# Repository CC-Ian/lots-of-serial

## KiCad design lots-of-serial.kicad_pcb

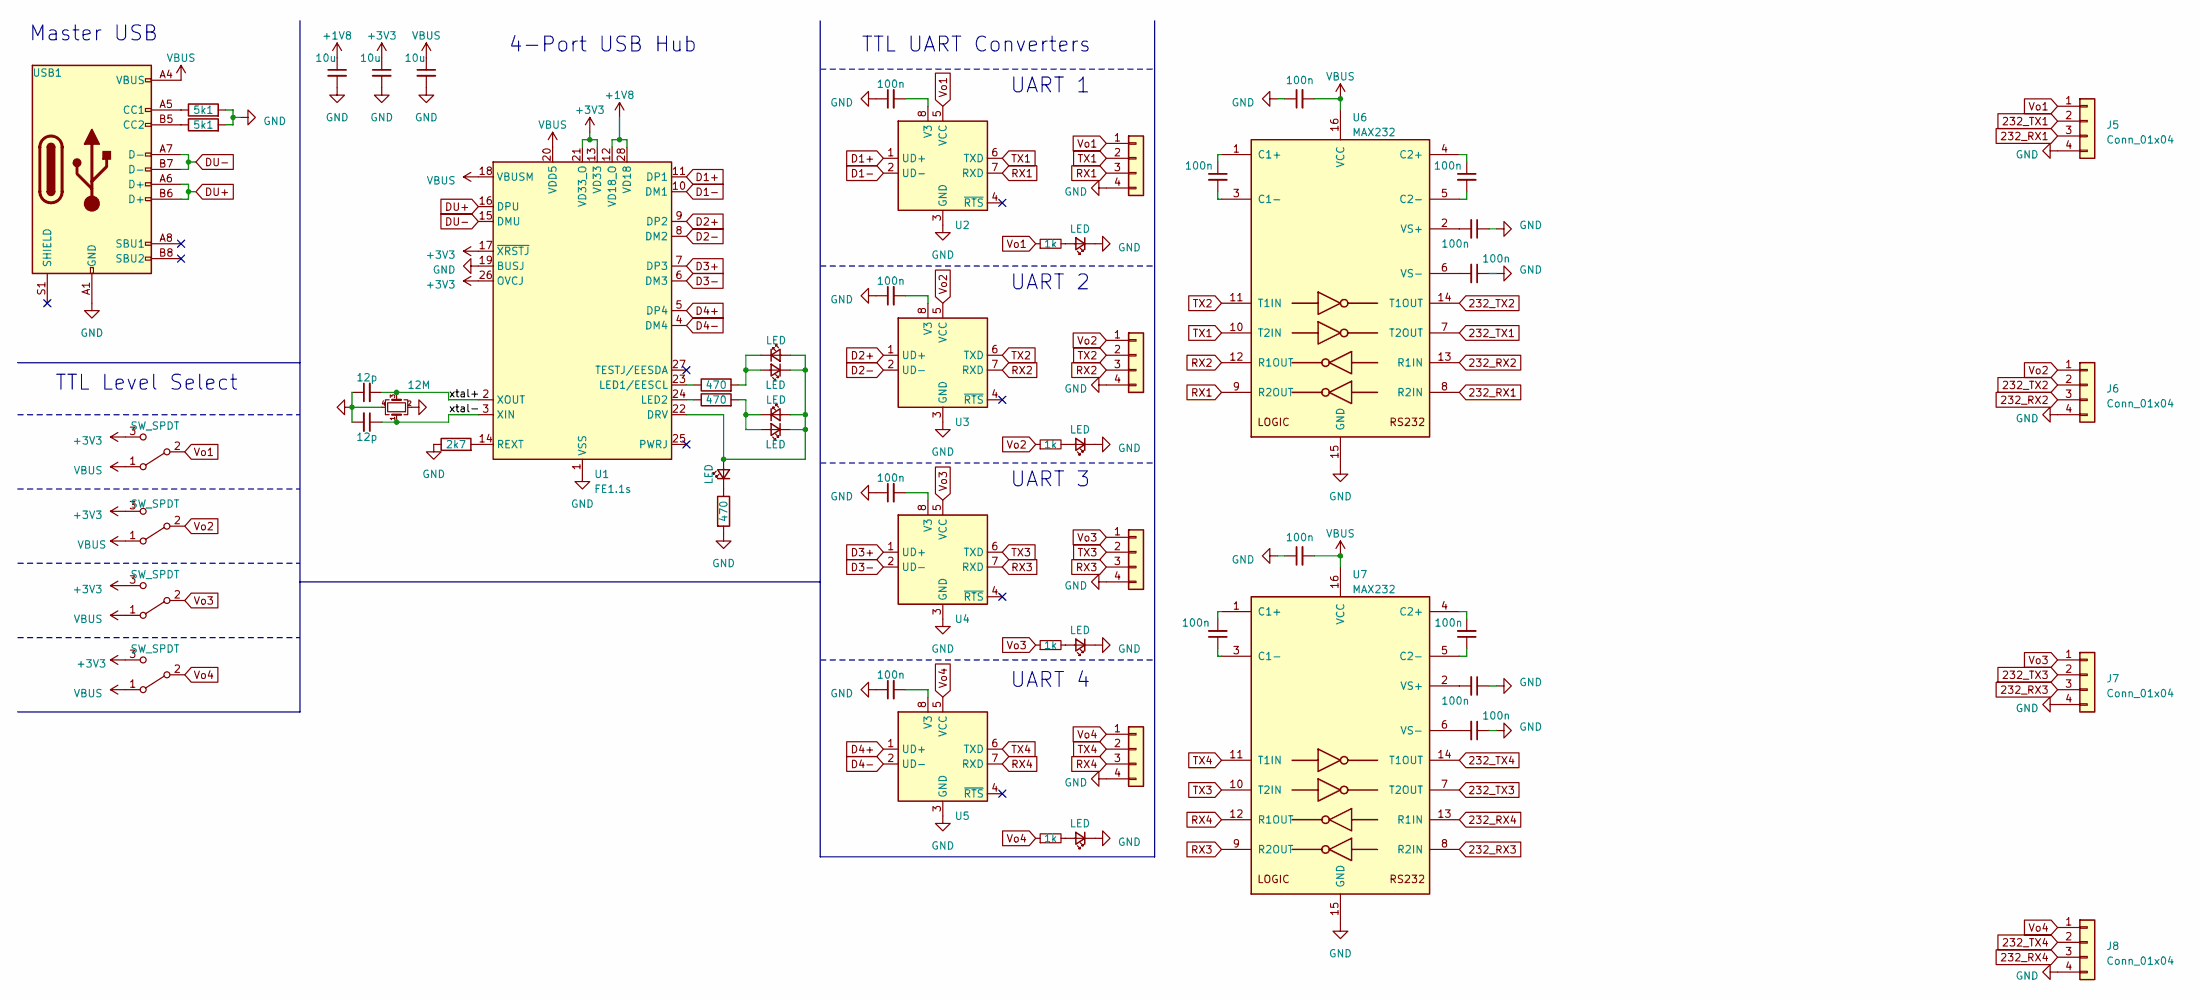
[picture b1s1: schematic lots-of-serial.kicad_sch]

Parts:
C1, C2: 12p; C_0402_1005Metric
C3, C4, C5: 10u; C_0402_1005Metric
C6, C7, C8, C9, C10, C11, C12, C13, C14, C15, C16, C17, C18, C19: 100n; C_0402_1005Metric
D1, D2, D3, D4, D5, D6, D7, D8, D9: LED; D_0402_1005Metric
J1, J2, J3, J4, J5, J6, J7, J8: Conn_01x04; PinHeader_1x04_P2.54mm_Vertical
R1, R2: 5k1; R_0402_1005Metric
R3: 2k7; R_0402_1005Metric
R4, R5, R6: 470; R_0402_1005Metric
R7, R8, R9, R10: 1k; R_0402_1005Metric
SW1, SW2, SW3, SW4: SW_SPDT; SW_SPDT_PCM12
U1: FE1.1s; SSOP-28_3.9x9.9mm_P0.635mm
U2, U3, U4, U5: SOP-8_3.9x4.9mm_P1.27mm
U6, U7: MAX232; SOIC-16_3.9x9.9mm_P1.27mm
USB1: USB_C_Receptacle_USB2.0; USB_C_Receptacle_HRO_TYPE-C-31-M-12
Y1: 12M; Crystal_SMD_3225-4Pin_3.2x2.5mm

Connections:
232_RX1: J5.3, U6.8 (R2IN)
232_RX2: J6.3, U6.13 (R1IN)
232_RX3: J7.3, U7.8 (R2IN)
232_RX4: J8.3, U7.13 (R1IN)
232_TX1: J5.2, U6.7 (T2OUT)
232_TX2: J6.2, U6.14 (T1OUT)
232_TX3: J7.2, U7.7 (T2OUT)
232_TX4: J8.2, U7.14 (T1OUT)
+1V8: C3.1, U1.12 (VD18_O), U1.28 (VD18)
+3V3: C4.1, SW1.3 (C), SW2.3 (C), SW3.3 (C), SW4.3 (C), U1.13 (VD33), U1.17 (~XRSTJ), U1.21 (VD33_O), U1.26 (OVCJ)
/xtal+: C1.2, U1.2 (XOUT), Y1.3
/xtal-: C2.1, U1.3 (XIN), Y1.1
D1+: U1.11 (DP1), U2.1 (UD+)
D1-: U1.10 (DM1), U2.2 (UD-)
D2+: U1.9 (DP2), U3.1 (UD+)
D2-: U1.8 (DM2), U3.2 (UD-)
D3+: U1.7 (DP3), U4.1 (UD+)
D3-: U1.6 (DM3), U4.2 (UD-)
D4+: U1.5 (DP4), U5.1 (UD+)
D4-: U1.4 (DM4), U5.2 (UD-)
DU+: U1.16 (DPU), USB1.A6 (D+), USB1.B6 (D+)
DU-: U1.15 (DMU), USB1.A7 (D-), USB1.B7 (D-)
GND: C1.1, C2.2, C3.2, C4.2, C5.2, C6.1, C7.1, C8.1, C9.1, C12.1, C13.1, C16.1, C17.1, C18.1, C19.1, D6.1 (K), D7.1 (K), D8.1 (K), D9.1 (K), J1.4, J2.4, J3.4, J4.4, J5.4, J6.4, J7.4, J8.4, R1.2, R2.2, R3.1, R6.2, U1.1 (VSS), U1.19 (BUSJ), U2.3 (GND), U3.3 (GND), U4.3 (GND), U5.3 (GND), U6.15 (GND), U7.15 (GND), USB1.A1 (GND), USB1.A12 (GND), USB1.B1 (GND), USB1.B12 (GND), Y1.2, Y1.4
unnamed: D1.2 (A), D2.1 (K), D3.2 (A), D4.1 (K), D5.2 (A), U1.22 (DRV)
unnamed: D1.1 (K), D2.2 (A), R4.2
unnamed: D3.1 (K), D4.2 (A), R5.2
unnamed: D5.1 (K), R6.1
unnamed: D6.2 (A), R7.2
unnamed: D7.2 (A), R8.2
unnamed: D8.2 (A), R9.2
unnamed: D9.2 (A), R10.2
unnamed: R4.1, U1.23 (LED1/EESCL)
unnamed: R5.1, U1.24 (LED2)
unnamed: R3.2, U1.14 (REXT)
unnamed: C6.2, U2.8 (V3)
unnamed: C7.2, U3.8 (V3)
unnamed: C8.2, U4.8 (V3)
unnamed: C9.2, U5.8 (V3)
unnamed: C10.1, U6.1 (C1+)
unnamed: C10.2, U6.3 (C1-)
unnamed: C11.1, U6.4 (C2+)
unnamed: C11.2, U6.5 (C2-)
unnamed: C18.2, U6.2 (VS+)
unnamed: C19.2, U6.6 (VS-)
unnamed: C14.2, U7.1 (C1+)
unnamed: C14.1, U7.3 (C1-)
unnamed: C15.2, U7.4 (C2+)
unnamed: C15.1, U7.5 (C2-)
unnamed: C16.2, U7.2 (VS+)
unnamed: C17.2, U7.6 (VS-)
unnamed: R1.1, USB1.A5 (CC1)
unnamed: R2.1, USB1.B5 (CC2)
RX1: J4.3, U2.7 (RXD), U6.9 (R2OUT)
RX2: J3.3, U3.7 (RXD), U6.12 (R1OUT)
RX3: J2.3, U4.7 (RXD), U7.9 (R2OUT)
RX4: J1.3, U5.7 (RXD), U7.12 (R1OUT)
TX1: J4.2, U2.6 (TXD), U6.10 (T2IN)
TX2: J3.2, U3.6 (TXD), U6.11 (T1IN)
TX3: J2.2, U4.6 (TXD), U7.10 (T2IN)
TX4: J1.2, U5.6 (TXD), U7.11 (T1IN)
VBUS: C5.1, C12.2, C13.2, SW1.1 (A), SW2.1 (A), SW3.1 (A), SW4.1 (A), U1.18 (VBUSM), U1.20 (VDD5), U6.16 (VCC), U7.16 (VCC), USB1.A4 (VBUS), USB1.A9 (VBUS), USB1.B4 (VBUS), USB1.B9 (VBUS)
Vo1: J4.1, J5.1, R7.1, SW1.2 (B), U2.5 (VCC)
Vo2: J3.1, J6.1, R8.1, SW2.2 (B), U3.5 (VCC)
Vo3: J2.1, J7.1, R9.1, SW3.2 (B), U4.5 (VCC)
Vo4: J1.1, J8.1, R10.1, SW4.2 (B), U5.5 (VCC)

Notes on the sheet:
UART 4
TTL UART Converters
UART 1
4-Port USB Hub
Master USB
UART 3
UART 2
TTL Level Select

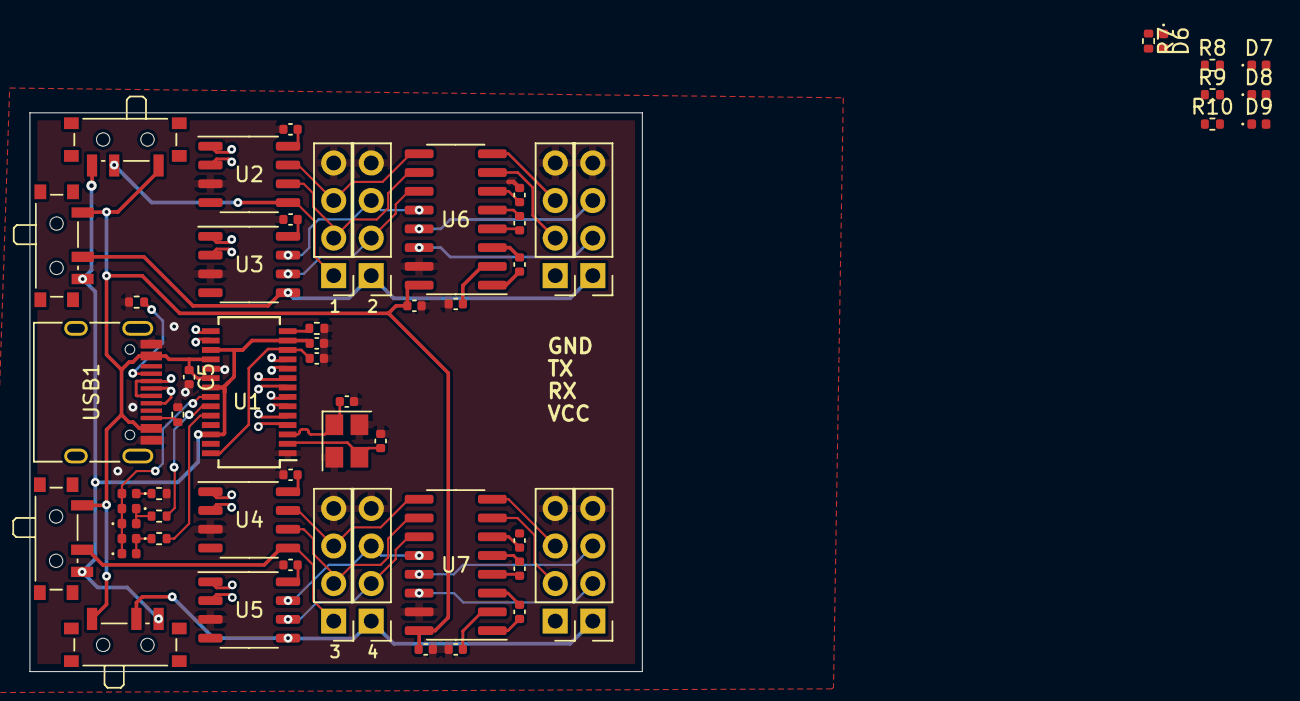
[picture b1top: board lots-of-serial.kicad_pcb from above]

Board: 6 copper layers, 41.4 x 37.8 mm, 59 parts (0 on the bottom side), 65 nets.

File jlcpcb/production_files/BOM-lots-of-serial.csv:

Comment,Designator,Footprint,LCSC
~,U5,SOP-8_3.9x4.9mm_P1.27mm,
100n,C19,C_0402_1005Metric,
100n,C18,C_0402_1005Metric,
100n,C17,C_0402_1005Metric,
100n,C16,C_0402_1005Metric,
100n,C15,C_0402_1005Metric,
100n,C14,C_0402_1005Metric,
100n,C13,C_0402_1005Metric,
100n,C12,C_0402_1005Metric,
100n,C11,C_0402_1005Metric,
100n,C10,C_0402_1005Metric,
Conn_01x04,J5,PinHeader_1x04_P2.54mm_Vertical,
Conn_01x04,J8,PinHeader_1x04_P2.54mm_Vertical,
Conn_01x04,J7,PinHeader_1x04_P2.54mm_Vertical,
Conn_01x04,J6,PinHeader_1x04_P2.54mm_Vertical,
~,U3,SOP-8_3.9x4.9mm_P1.27mm,
SW_SPDT,SW1,SW_SPDT_PCM12,
SW_SPDT,SW2,SW_SPDT_PCM12,
SW_SPDT,SW3,SW_SPDT_PCM12,
SW_SPDT,SW4,SW_SPDT_PCM12,
Conn_01x04,J4,PinHeader_1x04_P2.54mm_Vertical,
Conn_01x04,J1,PinHeader_1x04_P2.54mm_Vertical,
Conn_01x04,J2,PinHeader_1x04_P2.54mm_Vertical,
Conn_01x04,J3,PinHeader_1x04_P2.54mm_Vertical,
12p,C1,C_0402_1005Metric,
2k7,R3,R_0402_1005Metric,
LED,D4,D_0402_1005Metric,
100n,C8,C_0402_1005Metric,
LED,D5,D_0402_1005Metric,
5k1,R1,R_0402_1005Metric,
12p,C2,C_0402_1005Metric,
USB_C_Receptacle_USB2.0,USB1,USB_C_Receptacle_HRO_TYPE-C-31-M-12,
470,R4,R_0402_1005Metric,
~,U2,SOP-8_3.9x4.9mm_P1.27mm,
10u,C4,C_0402_1005Metric,
FE1.1s,U1,SSOP-28_3.9x9.9mm_P0.635mm,
MAX232,U6,SOIC-16_3.9x9.9mm_P1.27mm,
100n,C7,C_0402_1005Metric,
10u,C3,C_0402_1005Metric,
MAX232,U7,SOIC-16_3.9x9.9mm_P1.27mm,
~,U4,SOP-8_3.9x4.9mm_P1.27mm,
470,R5,R_0402_1005Metric,
10u,C5,C_0402_1005Metric,
100n,C9,C_0402_1005Metric,
LED,D2,D_0402_1005Metric,
LED,D1,D_0402_1005Metric,
470,R6,R_0402_1005Metric,
100n,C6,C_0402_1005Metric,
LED,D3,D_0402_1005Metric,
5k1,R2,R_0402_1005Metric,
12M,Y1,Crystal_SMD_3225-4Pin_3.2x2.5mm,

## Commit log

2023-05-19 Commit message. Stuff has happened. Not sure what. I think it's the middle of board version 3.0 now
2023-07-09 Likely acceptable version 2
2023-07-09 Added gitignore
